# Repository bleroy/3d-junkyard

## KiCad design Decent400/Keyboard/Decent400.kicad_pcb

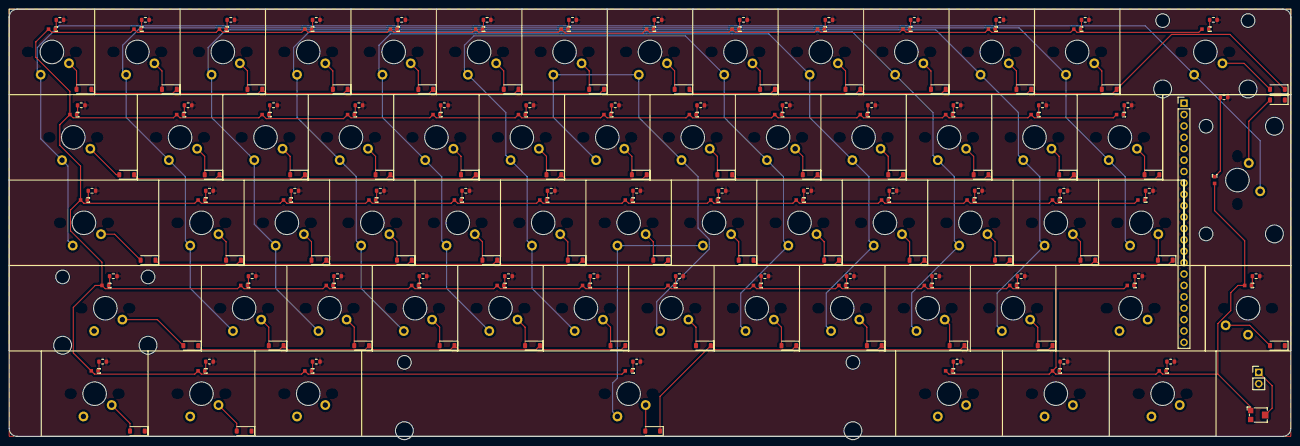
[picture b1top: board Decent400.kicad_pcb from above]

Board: 2 copper layers, 285.8 x 95.3 mm, 181 parts (0 on the bottom side), 142 nets.

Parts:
D1, D2, D3, D4, D5, D6, D7, D8, D9, D10, D11, D12, D13, D14, D15, D16, D17, D18, D19, D20, D21, D22, D23, D24, D25, D26, D27, D28, D29, D30, D31, D32, D33, D34, D35, D36, D37, D38, D39, D40, D41, D42, D43, D44, D45, D46, D47, D48, D49, D50, D51, D52, D53, D54, D55, D56: 1N4148W; D_SOD-123
J1: Conn_01x22; PinHeader_1x22_P2.54mm_Vertical
J2: Conn_01x02_Pin; PinHeader_1x02_P2.54mm_Vertical
R1, R2, R4, R5, R6, R7, R8, R9, R10, R11, R12, R13, R14, R15, R16, R17, R18, R19, R20, R21, R22, R23, R24, R25, R26, R27, R28, R29, R30, R31, R32, R33, R34, R35, R36, R37, R38, R39, R40, R41, R42, R43, R44, R45, R46, R47, R48, R49, R50, R51, R52, R53, R54, R55, R56, R57, R58, R61, R62, R63, R64: 100; R_0603_1608Metric
RV1: R_Potentiometer; Potentiometer_Bourns_TC33X_Vertical
SW0: 0; MX-1-00U-LED
SW1: 1; MX-1-00U-LED
SW2: 2; MX-1-00U-LED
SW3: 3; MX-1-00U-LED
SW4: 4; MX-1-00U-LED
SW5: 5; MX-1-00U-LED
SW6: 6; MX-1-00U-LED
SW7: 7; MX-1-00U-LED
SW8: 8; MX-1-00U-LED
SW9: 9; MX-1-00U-LED
SWA1: A; MX-1-00U-LED
SWB1: B; MX-1-00U-LED
SWBrk1: Break; MX-1-25U-LED
SWC1: C; MX-1-00U-LED
SWComma1: Comma; MX-1-00U-LED
SWCps1: Caps; MX-1-75U-LED
SWCtl1: Control; MX-1-25U-LED
SWD1: D; MX-1-00U-LED
SWDash1: Dash; MX-1-00U-LED
SWDel1: Del; MX-2-00U-LED
SWE1: E; MX-1-00U-LED
SWEqual1: Equal; MX-1-00U-LED
SWEsc1: Esc; MX-1-00U-LED
SWF1: F; MX-1-00U-LED
SWG1: G; MX-1-00U-LED
SWGT1: GreaterThan; MX-1-00U-LED
SWH1: H; MX-1-00U-LED
SWI1: I; MX-1-00U-LED
SWInv1: Atari; Choc-1-00U-LED
SWJ1: J; MX-1-00U-LED
SWK1: K; MX-1-00U-LED
SWL1: L; MX-1-00U-LED
SWLT1: LessThan; MX-1-00U-LED
SWLeftSft1: Shift; MX-2-25U-LED
SWM1: M; MX-1-00U-LED
SWN1: N; MX-1-00U-LED
SWO1: O; MX-1-00U-LED
SWOption1: Option; MX-1-25U-LED
SWP1: P; MX-1-00U-LED
SWPeriod1: Period; MX-1-00U-LED
SWPlus1: Plus; MX-1-00U-LED
SWQ1: Q; MX-1-00U-LED
SWR1: R; MX-1-00U-LED
SWReset1: Reset; MX-1-25U-LED
SWRet1: Return; MX-ISO-RETURN
SWRightSft1: Shift; MX-1-75U-LED
SWS1: S; MX-1-00U-LED
SWSelect1: Select; MX-1-25U-LED
SWSemi1: Semicolon; MX-1-00U-LED
SWSlash1: Slash; MX-1-00U-LED
SWSpc1: Space; MX-6-25U-LED
SWStar1: Star; MX-1-00U-LED
SWStart1: Start; MX-1-25U-LED
SWT1: T; MX-1-00U-LED
SWTab1: Tab; MX-1-50U-LED
SWU1: U; MX-1-00U-LED
SWV1: V; MX-1-00U-LED
SWW1: W; MX-1-00U-LED
SWX1: X; MX-1-00U-LED
SWY1: Y; MX-1-00U-LED
SWZ1: Z; MX-1-00U-LED

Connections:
5V: J2.1, RV1.2
COL_1: J1.10, SW6.1, SW7.1, SWN1.1, SWU1.1, SWY1.1
COL_2: J1.11, SWH1.1, SWJ1.1, SWSpc1.1
COL_3: J1.12, SW5.1, SW8.1, SWB1.1, SWG1.1, SWI1.1, SWK1.1, SWM1.1, SWT1.1
COL_4: J1.13, SW4.1, SW9.1, SWComma1.1, SWF1.1, SWL1.1, SWO1.1, SWR1.1, SWV1.1
COL_5: J1.14, SW0.1, SW3.1, SWC1.1, SWD1.1, SWE1.1, SWP1.1, SWPeriod1.1, SWSemi1.1
COL_6: J1.15, SW2.1, SWDash1.1, SWLT1.1, SWPlus1.1, SWS1.1, SWSlash1.1, SWW1.1, SWX1.1
COL_7: J1.16, SW1.1, SWA1.1, SWEqual1.1, SWGT1.1, SWInv1.1, SWQ1.1, SWStar1.1, SWZ1.1
COL_8: J1.17, SWCps1.1, SWDel1.1, SWEsc1.1, SWRet1.1, SWTab1.1
COL_9: J1.9, SWBrk1.1, SWCtl1.1, SWLeftSft1.1, SWRightSft1.1
GND: J1.18, SWOption1.2, SWReset1.2, SWSelect1.2, SWStart1.2
LED_GND: J2.2, R1.2, R2.2, R4.2, R5.2, R6.2, R7.2, R8.2, R9.2, R10.2, R11.2, R12.2, R13.2, R14.2, R15.2, R16.2, R17.2, R18.2, R19.2, R20.2, R21.2, R22.2, R23.2, R24.2, R25.2, R26.2, R27.2, R28.2, R29.2, R30.2, R31.2, R32.2, R33.2, R34.2, R35.2, R36.2, R37.2, R38.2, R39.2, R40.2, R41.2, R42.2, R43.2, R44.2, R45.2, R46.2, R47.2, R48.2, R49.2, R50.2, R51.2, R52.2, R53.2, R54.2, R55.2, R56.2, R57.2, R58.2, R61.2, R62.2, R63.2, R64.2
unnamed: D1.2 (A), SWBrk1.2
unnamed: D2.2 (A), SWCtl1.2
unnamed: D3.2 (A), SWLeftSft1.2, SWRightSft1.2
unnamed: D4.2 (A), SW7.2
unnamed: D5.2 (A), SW6.2
unnamed: D6.2 (A), SWU1.2
unnamed: D7.2 (A), SWY1.2
unnamed: D8.2 (A), SWN1.2
unnamed: D9.2 (A), SWJ1.2
unnamed: D10.2 (A), SWH1.2
unnamed: D11.2 (A), SWSpc1.2
unnamed: D12.2 (A), SW8.2
unnamed: D13.2 (A), SW5.2
unnamed: D14.2 (A), SWI1.2
unnamed: D15.2 (A), SWT1.2
unnamed: D16.2 (A), SWK1.2
unnamed: D17.2 (A), SWG1.2
unnamed: D18.2 (A), SWM1.2
unnamed: D19.2 (A), SWB1.2
unnamed: D20.2 (A), SW9.2
unnamed: D21.2 (A), SW4.2
unnamed: D22.2 (A), SWO1.2
unnamed: D23.2 (A), SWR1.2
unnamed: D24.2 (A), SWL1.2
unnamed: D25.2 (A), SWF1.2
unnamed: D26.2 (A), SWComma1.2
unnamed: D27.2 (A), SWV1.2
unnamed: D28.2 (A), SW0.2
unnamed: D29.2 (A), SW3.2
unnamed: D30.2 (A), SWP1.2
unnamed: D31.2 (A), SWE1.2
unnamed: D32.2 (A), SWSemi1.2
unnamed: D33.2 (A), SWD1.2
unnamed: D34.2 (A), SWPeriod1.2
unnamed: D35.2 (A), SWC1.2
unnamed: D36.2 (A), SWLT1.2
unnamed: D37.2 (A), SW2.2
unnamed: D38.2 (A), SWDash1.2
unnamed: D39.2 (A), SWW1.2
unnamed: D40.2 (A), SWPlus1.2
unnamed: D41.2 (A), SWS1.2
unnamed: D42.2 (A), SWSlash1.2
unnamed: D43.2 (A), SWX1.2
unnamed: D44.2 (A), SWGT1.2
unnamed: D45.2 (A), SW1.2
unnamed: D46.2 (A), SWEqual1.2
unnamed: D47.2 (A), SWQ1.2
unnamed: D48.2 (A), SWStar1.2
unnamed: D49.2 (A), SWA1.2
unnamed: D50.2 (A), SWInv1.2
unnamed: D51.2 (A), SWZ1.2
unnamed: D52.2 (A), SWDel1.2
unnamed: D53.2 (A), SWEsc1.2
unnamed: D54.2 (A), SWRet1.2
unnamed: D55.2 (A), SWTab1.2
unnamed: D56.2 (A), SWCps1.2
unnamed: R1.1, SWBrk1.3
unnamed: R2.1, SWCtl1.3
unnamed: R4.1, SWLeftSft1.3
unnamed: R5.1, SWRightSft1.3
unnamed: R6.1, SW7.3
unnamed: R7.1, SW6.3
unnamed: R8.1, SWU1.3
unnamed: R9.1, SWY1.3
unnamed: R10.1, SWN1.3
unnamed: R11.1, SWJ1.3
unnamed: R12.1, SWH1.3
unnamed: R13.1, SWSpc1.3
unnamed: R14.1, SW8.3
unnamed: R15.1, SW5.3
unnamed: R16.1, SWI1.3
unnamed: R17.1, SWT1.3
unnamed: R18.1, SWK1.3
unnamed: R19.1, SWG1.3
unnamed: R20.1, SWM1.3
unnamed: R21.1, SWB1.3
unnamed: R22.1, SW9.3
unnamed: R23.1, SW4.3
unnamed: R24.1, SWO1.3
unnamed: R25.1, SWR1.3
unnamed: R26.1, SWL1.3
unnamed: R27.1, SWF1.3
unnamed: R28.1, SWComma1.3
unnamed: R29.1, SWV1.3
unnamed: R30.1, SW0.3
unnamed: R31.1, SW3.3
unnamed: R32.1, SWP1.3
unnamed: R33.1, SWE1.3
unnamed: R34.1, SWSemi1.3
unnamed: R35.1, SWD1.3
unnamed: R36.1, SWPeriod1.3
unnamed: R37.1, SWC1.3
unnamed: R38.1, SWLT1.3
unnamed: R39.1, SW2.3
unnamed: R40.1, SWDash1.3
unnamed: R41.1, SWW1.3
unnamed: R42.1, SWPlus1.3
unnamed: R43.1, SWS1.3
unnamed: R44.1, SWSlash1.3
unnamed: R45.1, SWX1.3
unnamed: R46.1, SWGT1.3
unnamed: R47.1, SW1.3
unnamed: R48.1, SWEqual1.3
unnamed: R49.1, SWQ1.3
unnamed: R50.1, SWStar1.3
unnamed: R51.1, SWA1.3
unnamed: R52.1, SWInv1.3
unnamed: R53.1, SWZ1.3
unnamed: R54.1, SWDel1.3
unnamed: R55.1, SWEsc1.3
unnamed: R56.1, SWRet1.3
unnamed: R57.1, SWTab1.3
unnamed: R58.1, SWCps1.3
unnamed: R61.1, SWStart1.3
unnamed: R62.1, SWSelect1.3
unnamed: R63.1, SWOption1.3
unnamed: R64.1, SWReset1.3
OPTION: J1.21, SWOption1.1
RESET: J1.22, SWReset1.1
ROW_1: D1.1 (K), D4.1 (K), D12.1 (K), D20.1 (K), D28.1 (K), D36.1 (K), D44.1 (K), D52.1 (K), J1.1
ROW_2: D5.1 (K), D13.1 (K), D21.1 (K), D29.1 (K), D37.1 (K), D45.1 (K), D53.1 (K), J1.2
ROW_3: D6.1 (K), D14.1 (K), D22.1 (K), D30.1 (K), D38.1 (K), D46.1 (K), D54.1 (K), J1.3
ROW_4: D7.1 (K), D15.1 (K), D23.1 (K), D31.1 (K), D39.1 (K), D47.1 (K), D55.1 (K), J1.4
ROW_5: D2.1 (K), D9.1 (K), D16.1 (K), D24.1 (K), D32.1 (K), D40.1 (K), D48.1 (K), J1.5
ROW_6: D10.1 (K), D17.1 (K), D25.1 (K), D33.1 (K), D41.1 (K), D49.1 (K), D56.1 (K), J1.6
ROW_7: D8.1 (K), D11.1 (K), D18.1 (K), D26.1 (K), D34.1 (K), D42.1 (K), D50.1 (K), J1.7
ROW_8: D3.1 (K), D19.1 (K), D27.1 (K), D35.1 (K), D43.1 (K), D51.1 (K), J1.8
SELECT: J1.20, SWSelect1.1
START: J1.19, SWStart1.1
VCC_LED: RV1.1, SW0.4, SW1.4, SW2.4, SW3.4, SW4.4, SW5.4, SW6.4, SW7.4, SW8.4, SW9.4, SWA1.4, SWB1.4, SWBrk1.4, SWC1.4, SWComma1.4, SWCps1.4, SWCtl1.4, SWD1.4, SWDash1.4, SWDel1.4, SWE1.4, SWEqual1.4, SWEsc1.4, SWF1.4, SWG1.4, SWGT1.4, SWH1.4, SWI1.4, SWInv1.4, SWJ1.4, SWK1.4, SWL1.4, SWLT1.4, SWLeftSft1.4, SWM1.4, SWN1.4, SWO1.4, SWOption1.4, SWP1.4, SWPeriod1.4, SWPlus1.4, SWQ1.4, SWR1.4, SWReset1.4, SWRet1.4, SWRightSft1.4, SWS1.4, SWSelect1.4, SWSemi1.4, SWSlash1.4, SWSpc1.4, SWStar1.4, SWStart1.4, SWT1.4, SWTab1.4, SWU1.4, SWV1.4, SWW1.4, SWX1.4, SWY1.4, SWZ1.4

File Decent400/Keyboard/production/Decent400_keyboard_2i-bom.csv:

Designator,Footprint,Quantity,Value,LCSC Part #
"D1, D10, D11, D12, D13, D14, D15, D16, D17, D18, D19, D2, D20, D21, D22, D23, D24, D25, D26, D27, D28, D29, D3, D30, D31, D32, D33, D34, D35, D36, D37, D38, D39, D4, D40, D41, D42, D43, D44, D45, D46, D47, D48, D49, D5, D50, D51, D52, D53, D54, D55, D56, D6, D7, D8, D9",D_SOD-123,56,1N4148W,C81598
J1,PinHeader_1x22_P2.54mm_Vertical,1,Conn_01x22,
"R1, R10, R11, R12, R13, R14, R15, R16, R17, R18, R19, R2, R20, R21, R22, R23, R24, R25, R26, R27, R28, R29, R3, R30, R31, R32, R33, R34, R35, R36, R37, R38, R39, R4, R40, R41, R42, R43, R44, R45, R46, R47, R48, R49, R5, R50, R51, R52, R53, R54, R55, R56, R57, R58, R6, R61, R62, R63, R64, R7, R8, R9",0603,62,100,C22775
RV1,Potentiometer_Bourns_TC33X_Vertical,1,R_Potentiometer,C720647
SW0,MX-1-00U-LED-UPSIDE-DOWN,1,0,C193191
SW1,MX-1-00U-LED-UPSIDE-DOWN,1,1,C193191
SW2,MX-1-00U-LED-UPSIDE-DOWN,1,2,C193191
SW3,MX-1-00U-LED-UPSIDE-DOWN,1,3,C193191
SW4,MX-1-00U-LED-UPSIDE-DOWN,1,4,C193191
SW5,MX-1-00U-LED-UPSIDE-DOWN,1,5,C193191
SW6,MX-1-00U-LED-UPSIDE-DOWN,1,6,C193191
SW7,MX-1-00U-LED-UPSIDE-DOWN,1,7,C193191
SW8,MX-1-00U-LED-UPSIDE-DOWN,1,8,C193191
SW9,MX-1-00U-LED-UPSIDE-DOWN,1,9,C193191
SWA1,MX-1-00U-LED-UPSIDE-DOWN,1,A,C193191
SWB1,MX-1-00U-LED-UPSIDE-DOWN,1,B,C193191
SWBrk1,MX-1-25U-LED-REVERSED,1,Break,C193191
SWC1,MX-1-00U-LED-UPSIDE-DOWN,1,C,C193191
SWComma1,MX-1-00U-LED-UPSIDE-DOWN,1,Comma,C193191
SWCps1,MX-1-00U-LED-UPSIDE-DOWN,1,Caps,C193191
"SWCtl1, SWCtl2",MX-1-25U-LED-REVERSED,2,Control,C193191
SWD1,MX-1-00U-LED-UPSIDE-DOWN,1,D,C193191
SWDash1,MX-1-00U-LED-UPSIDE-DOWN,1,Dash,C193191
SWDel1,MX-1-75U-LED-REVERSED,1,Del,C193191
SWE1,MX-1-00U-LED-UPSIDE-DOWN,1,E,C193191
SWEqual1,MX-1-00U-LED-UPSIDE-DOWN,1,Equal,C193191
SWEsc1,MX-1-25U-LED-REVERSED,1,Esc,C193191
SWF1,MX-1-00U-LED-UPSIDE-DOWN,1,F,C193191
SWG1,MX-1-00U-LED-UPSIDE-DOWN,1,G,C193191
SWGT1,MX-1-00U-LED-UPSIDE-DOWN,1,GreaterThan,C193191
SWH1,MX-1-00U-LED-UPSIDE-DOWN,1,H,C193191
SWI1,MX-1-00U-LED-UPSIDE-DOWN,1,I,C193191
SWInv1,MX-1-00U-LED-UPSIDE-DOWN,1,Atari,C193191
SWJ1,MX-1-00U-LED-UPSIDE-DOWN,1,J,C193191
SWK1,MX-1-00U-LED-UPSIDE-DOWN,1,K,C193191
SWL1,MX-1-00U-LED-UPSIDE-DOWN,1,L,C193191
SWLT1,MX-1-00U-LED-UPSIDE-DOWN,1,LessThan,C193191
SWLeftSft1,MX-1-25U-LED-REVERSED,1,Shift,C193191
SWM1,MX-1-00U-LED-UPSIDE-DOWN,1,M,C193191
SWN1,MX-1-00U-LED-UPSIDE-DOWN,1,N,C193191
SWO1,MX-1-00U-LED-UPSIDE-DOWN,1,O,C193191
SWOption1,MX-1-00U-LED,1,Option,C193191
SWP1,MX-1-00U-LED-UPSIDE-DOWN,1,P,C193191
SWPeriod1,MX-1-00U-LED-UPSIDE-DOWN,1,Period,C193191
SWPlus1,MX-1-00U-LED-UPSIDE-DOWN,1,Plus,C193191
SWQ1,MX-1-00U-LED-UPSIDE-DOWN,1,Q,C193191
SWR1,MX-1-00U-LED-UPSIDE-DOWN,1,R,C193191
SWReset1,MX-1-00U-LED,1,Reset,C193191
SWRet1,MX-1-25U-LED-REVERSED,1,Return,C193191
SWRightSft1,MX-2-25U-LED-REVERSED,1,Shift,C193191
SWS1,MX-1-00U-LED-UPSIDE-DOWN,1,S,C193191
SWSelect1,MX-1-00U-LED,1,Select,C193191
SWSemi1,MX-1-00U-LED-UPSIDE-DOWN,1,Semicolon,C193191
SWSlash1,MX-1-00U-LED-UPSIDE-DOWN,1,Slash,C193191
SWSpc1,MX-6-25U-LED-REVERSED,1,Space,C193191
SWStar1,MX-1-00U-LED-UPSIDE-DOWN,1,Star,C193191
SWStart1,MX-1-00U-LED,1,Start,C193191
SWT1,MX-1-00U-LED-UPSIDE-DOWN,1,T,C193191
SWTab1,MX-1-25U-LED-REVERSED,1,Tab,C193191
SWU1,MX-1-00U-LED-UPSIDE-DOWN,1,U,C193191
SWV1,MX-1-00U-LED-UPSIDE-DOWN,1,V,C193191
SWW1,MX-1-00U-LED-UPSIDE-DOWN,1,W,C193191
SWX1,MX-1-00U-LED-UPSIDE-DOWN,1,X,C193191
SWY1,MX-1-00U-LED-UPSIDE-DOWN,1,Y,C193191
SWZ1,MX-1-00U-LED-UPSIDE-DOWN,1,Z,C193191

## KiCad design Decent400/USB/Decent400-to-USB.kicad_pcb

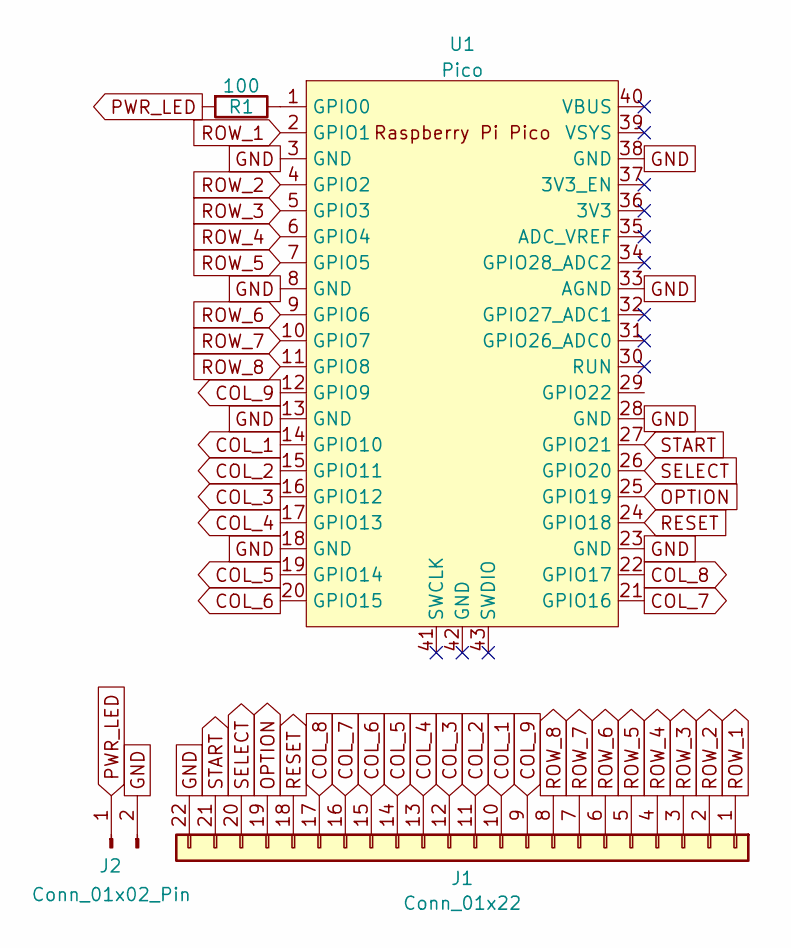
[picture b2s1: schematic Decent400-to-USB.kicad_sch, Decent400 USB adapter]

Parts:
J1: Conn_01x22; PinHeader_1x22_P2.54mm_Horizontal
J2: Conn_01x02_Pin; PinHeader_1x02_P2.54mm_Horizontal
R1: 100; R_Axial_DIN0411_L9.9mm_D3.6mm_P12.70mm_Horizontal
U1: Pico; RPi_Pico_SMD_TH

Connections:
COL_1: J1.10, U1.14 (GPIO10)
COL_2: J1.11, U1.15 (GPIO11)
COL_3: J1.12, U1.16 (GPIO12)
COL_4: J1.13, U1.17 (GPIO13)
COL_5: J1.14, U1.19 (GPIO14)
COL_6: J1.15, U1.20 (GPIO15)
COL_7: J1.16, U1.21 (GPIO16)
COL_8: J1.17, U1.22 (GPIO17)
COL_9: J1.9, U1.12 (GPIO9)
GND: J1.22, J2.2, U1.3 (GND), U1.8 (GND), U1.13 (GND), U1.18 (GND), U1.23 (GND), U1.28 (GND), U1.33 (AGND), U1.38 (GND)
unnamed: R1.1, U1.1 (GPIO0)
OPTION: J1.19, U1.25 (GPIO19)
PWR_LED: J2.1, R1.2
RESET: J1.18, U1.24 (GPIO18)
ROW_1: J1.1, U1.2 (GPIO1)
ROW_2: J1.2, U1.4 (GPIO2)
ROW_3: J1.3, U1.5 (GPIO3)
ROW_4: J1.4, U1.6 (GPIO4)
ROW_5: J1.5, U1.7 (GPIO5)
ROW_6: J1.6, U1.9 (GPIO6)
ROW_7: J1.7, U1.10 (GPIO7)
ROW_8: J1.8, U1.11 (GPIO8)
SELECT: J1.20, U1.26 (GPIO20)
START: J1.21, U1.27 (GPIO21)

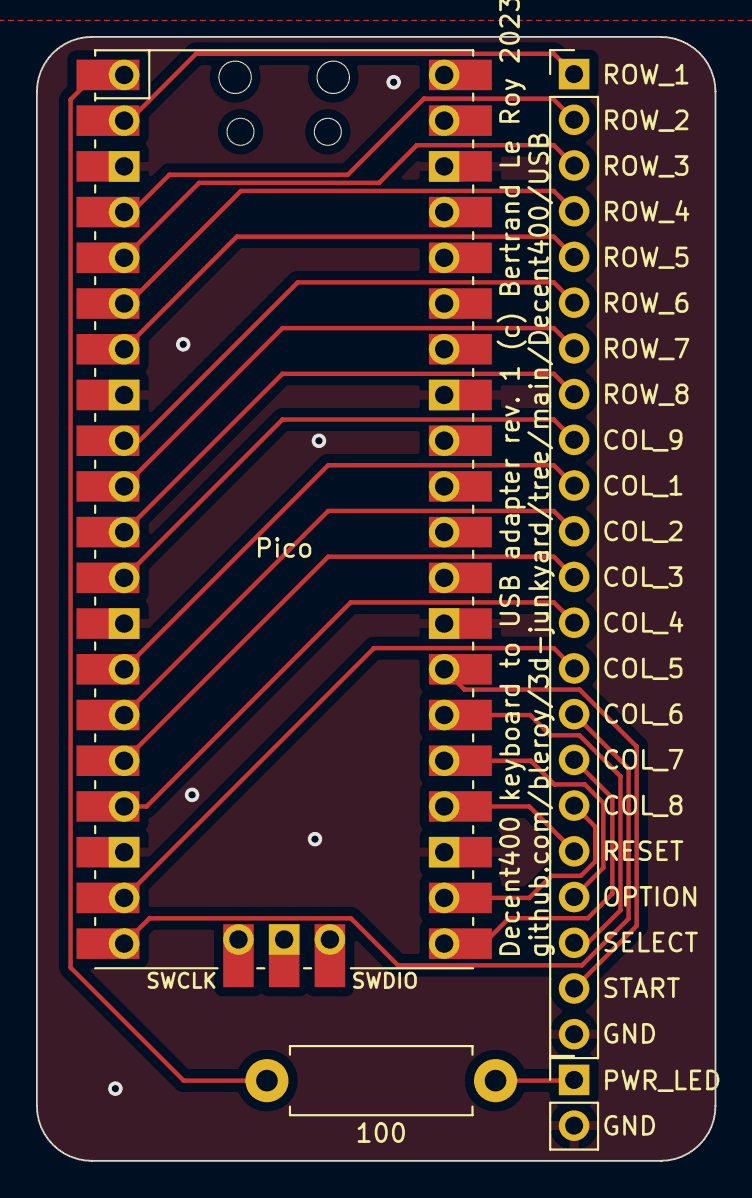
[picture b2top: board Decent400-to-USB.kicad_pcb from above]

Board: 2 copper layers, 37.7 x 62.4 mm, 4 parts (0 on the bottom side), 24 nets.
